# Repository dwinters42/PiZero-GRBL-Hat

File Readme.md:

# PiZero GRBL hat

This is a RaspberryPi Zero-compatible add-on board that can be used to
control up to 2 stepper motors using GCode commands. The board works
with the non-Wifi (Pi Zero) and the Wifi version (Pi Zero W), it
should also work with a standard Raspberrypi, although I have not
tested this.

The hat has an on-board AVR Mega328P micro-controller that runs the
[GRBL](https://github.com/grbl/grbl) firmware, 2 sockets for
Pololu-compatible Stepper boards and connectors for the stepper
motors, limit switches, stepper motor power and an extra I2C connector
that is wired to the Pi Zero I2C contacts.

The big benefit of this arrangement is that the AVR takes care of all
the timing-sensitive tasks, so that the Pi Zero can do other things.

# Building instructions
## Get components

See the bill of materials below.

## Assemble board

Use the [HTML-BOM](file:./bom_interactive.html) generated by the
brilliant [Interactive BOM KICAD plugin from
openscopeproject](https://github.com/openscopeproject/InteractiveHtmlBom)
to populate the board.

## Program firmware on AVR

## Mount the board

With the Raspberrypi turned off, plug the GRBL hat board into the Pi
header, so that the 2 boards are aligned to each other. Do not connect
anything to the GRBL hat yet.

## Pi Zero setup

In order for the communication to work, the on-board serial board of
the Raspberrypi has to be enabled with raspi-config: run raspi-config
in a terminal, go to Interfacing Options -> Serial -> No to login
shell -> Yes to enable serial port hardware. After rebooting, you
should have a new serial port accessible as /dev/ttyS0.

## Test serial connection

Connect to Grbl using the serial terminal of your choice. Set
the port to /dev/ttyS0 and the the baud rate to 115200, 8 bits, no
parity, 1 stop bit (8N1). One possibility is to use miniterm:

    miniterm /dev/ttyS0 115200

Once connected, you will not see anything (GRBL started when the Pi
was plugged into power).

Type $ and press enter to have GRBL print a help message. You should
not see any local echo of the $ and enter. Grbl should respond with:

    [HLP:$$ $# $G $I $N $x=val $Nx=line $J=line $SLP $C $X $H ~ ! ? ctrl-x]
    ok

Congratulations, you have a working GRBL controller connected to your
Pi Zero!

Shut down the Pi and disconnect power.

Next, connect two stepper driver boards (e.g. 2x Pololu DRV8825 driver
board). Make sure you get the orientation correct.

Then connect the motor power supply and set the current using the
trimpot on the driver boards. Disconnect motor power, plug in 2
stepper motors (e.g. NEMA17 form factor) and apply motor power again.

## First trial run

Turn on power to the Pi and log in via ssh. Run the following commands
from a terminal to test the motors:

    stty -F /dev/ttyS0 115200 # set baud rate to 115200 baud
	cat testing/test.gcode > /dev/ttyS0

This should move first the x-axis to 45 degrees and back, followed by
the y-axis. If there is jerky motion or no motion at all, make sure
that the wire connections to the steppers are good.

# Using the board

The Raspberrypi board communicates with the GRBL controller over the
on-board serial port /dev/ttyS0. The serial port needs to be
configured to 115200 baud, 8 databits, 1 stopbit, no parity (8N1).

The stepper resolution is set to 32 microsteps in hardware, this
cannot be changed. For a standard stepper with 200 steps per
revolution this gives 200*32/360 = 17.778 steps per degree.

Look at the well-maintained [GRBL
Wiki](https://github.com/gnea/grbl/wiki) for any GRBL related
questions.

# Bill of materials

|-------|-----|------------------|---------------------|--------------|-------------------|-------|
| Ref   | Qty | Value            | Part                | Manufacturer | Mouser            | Price |
|-------|-----|------------------|---------------------|--------------|-------------------|-------|
| A1    | 1   | AXIS_X           |                     | Pololu       |                   |       |
| A2    | 1   | AXIS_Y           |                     | Pololu       |                   |       |
| C1 C2 | 2   | 100n 0805        |                     |              |                   |       |
| C4 C5 | 2   | 33p 0805         |                     |              |                   |       |
| C8 C9 | 2   | 100u dia 6.3 25V |                     |              |                   |       |
| J1    | 1   | GPIO_CONNECTOR   | pin header 2x20     |              |                   |       |
| J2    | 1   | ISP              | pin header 2x03     |              |                   |       |
| J3    | 1   | LIMIT_X          | PH B2B 1x02 vert    | JST          |                   |       |
| J4    | 1   | LIMIT_Y          | PH B2B 1x02 vert    |              |                   |       |
| J5    | 1   | VMOT             | PH B2B 1x02 vert    |              |                   |       |
| J6    | 1   | MOTOR_X          | PH B2B 1x04 vert    |              |                   |       |
| J7    | 1   | MOTOR_Y          | PH B2B 1x04 vert    |              |                   |       |
| J8    | 1   | I2C              | PH B2B 1x04 vert    |              |                   |       |
| R1    | 1   | 1M 0805          |                     |              |                   |       |
| R2    | 1   | 10K 0805         |                     |              |                   |       |
| U1    | 1   | uC TQFP-32       | ATmega328P-AU       | Microchip    | 556-ATMEGA328P-AU | 1.81  |
| Y1    | 1   | 16MHz ABM3       | ABM3-16.000MHZ-B2-T | Abracon      | 815-ABM3-16-D2Y-T | 0.468 |
|-------|-----|------------------|---------------------|--------------|-------------------|-------|

# Todo for next revision

- add comment about 32 microsteps on schematics
- use less pins on the Raspi connector + cutout in PCB
- add missing mouser part numbers in BOM

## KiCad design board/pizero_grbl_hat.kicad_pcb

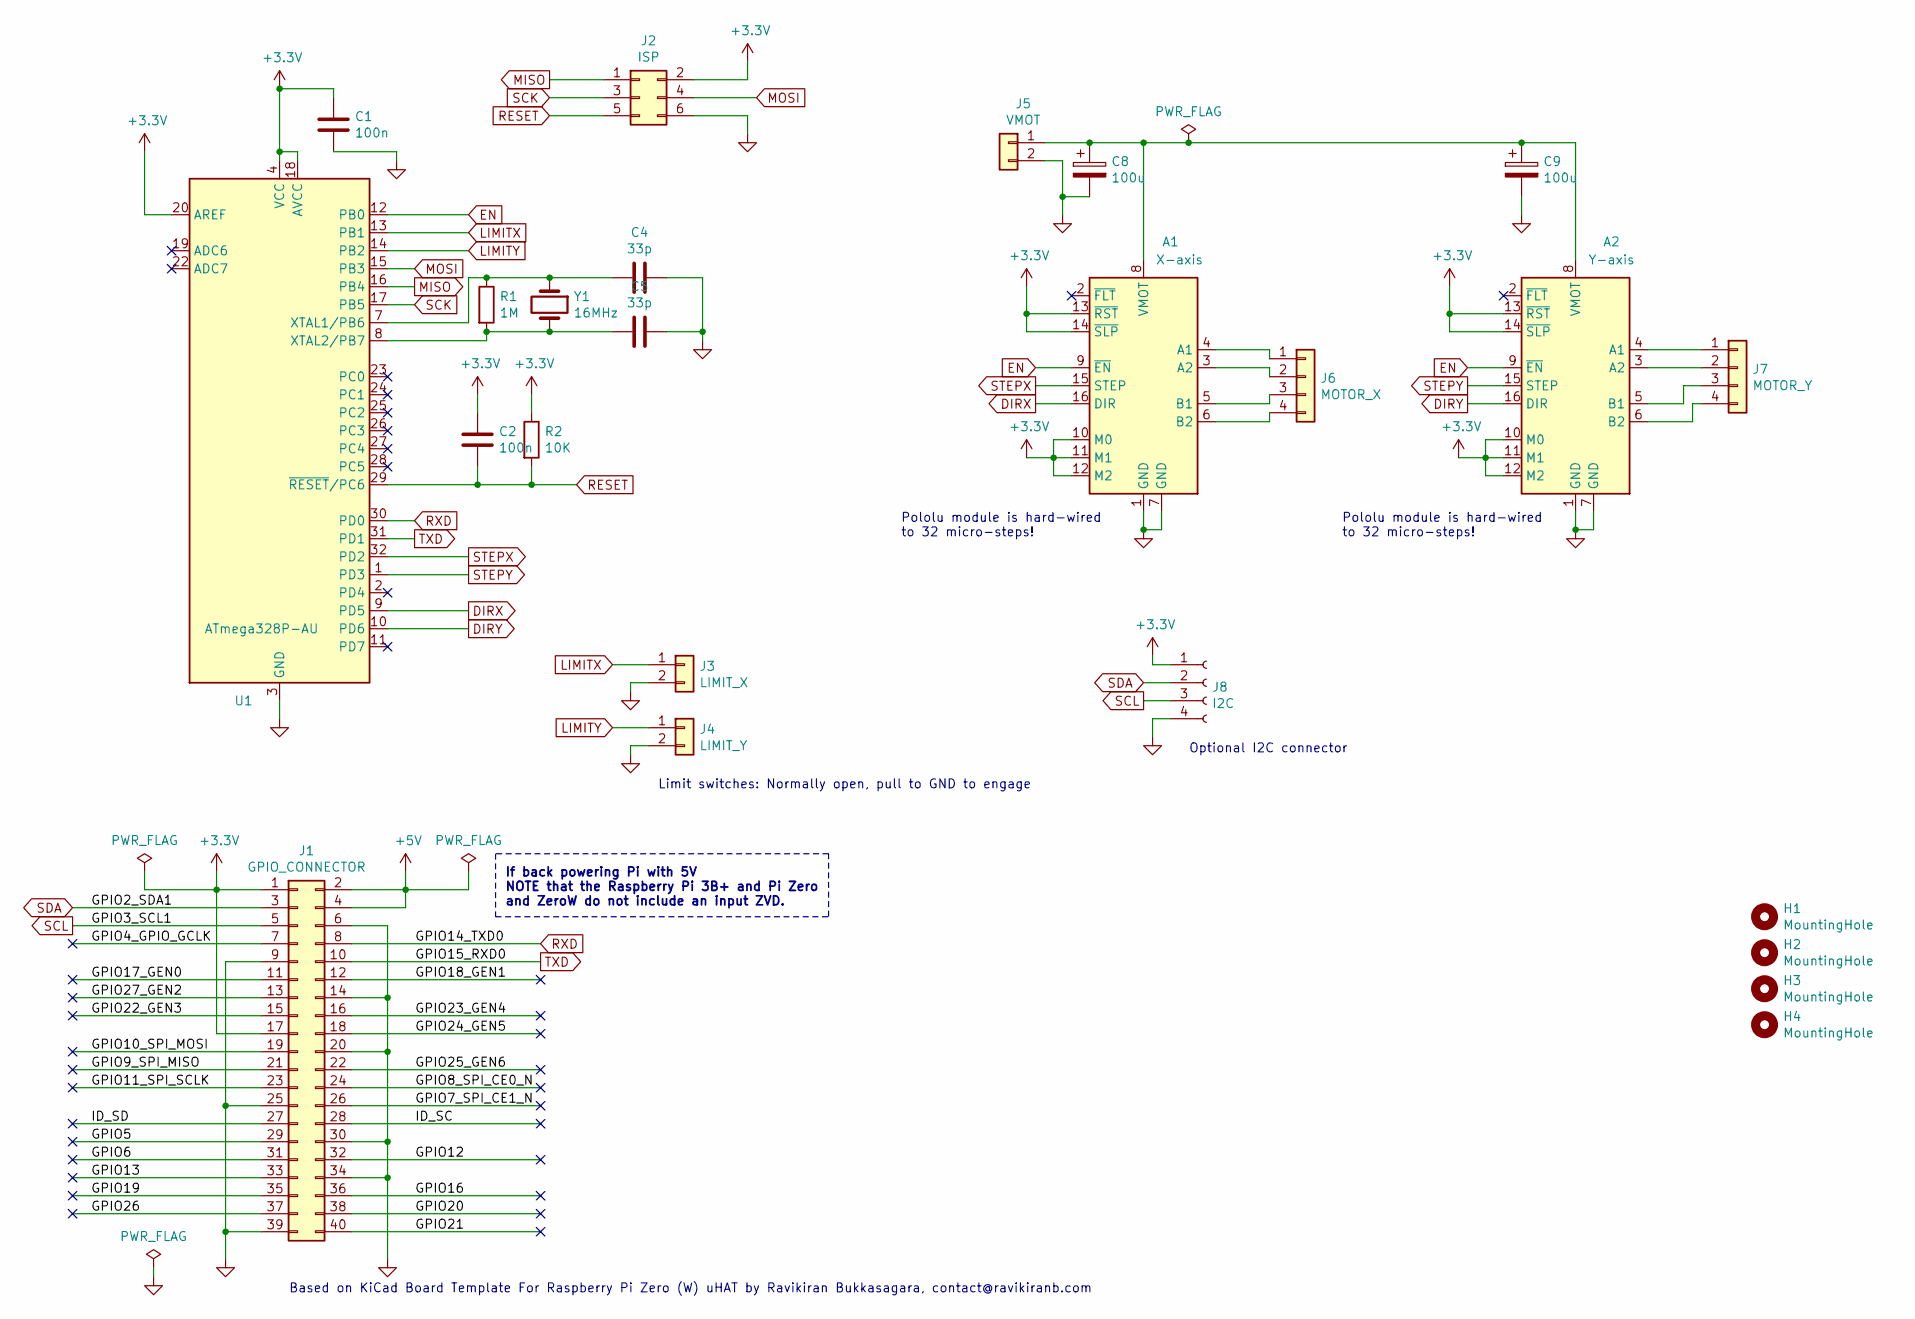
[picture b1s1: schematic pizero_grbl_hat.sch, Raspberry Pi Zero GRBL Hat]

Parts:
A1: X-axis; Pololu_Breakout-16_15.2x20.3mm
A2: Y-axis; Pololu_Breakout-16_15.2x20.3mm
C1: 100n; C_0805_2012Metric_Pad1.15x1.40mm_HandSolder
C2: 100n; C_0805_2012Metric
C4, C5: 33p; C_0805_2012Metric
C8, C9: 100u; CP_Elec_6.3x7.7
H1, H2, H3, H4: MountingHole; MountingHole_2.7mm_M2.5_uHAT_RPi
J1: GPIO_CONNECTOR; PinSocket_2x20_P2.54mm_Vertical_Centered_Anchor
J2: ISP; PinHeader_2x03_P2.54mm_Vertical
J3: LIMIT_X; JST_PH_B2B-PH-K_1x02_P2.00mm_Vertical
J4: LIMIT_Y; JST_PH_B2B-PH-K_1x02_P2.00mm_Vertical
J5: VMOT; JST_PH_B2B-PH-K_1x02_P2.00mm_Vertical
J6: MOTOR_X; JST_PH_B4B-PH-K_1x04_P2.00mm_Vertical
J7: MOTOR_Y; JST_PH_B4B-PH-K_1x04_P2.00mm_Vertical
J8: I2C; JST_PH_B4B-PH-K_1x04_P2.00mm_Vertical
R1: 1M; R_0805_2012Metric_Pad1.15x1.40mm_HandSolder
R2: 10K; R_0805_2012Metric
U1: ATmega328P-AU; TQFP-32_7x7mm_P0.8mm
Y1: 16MHz; Crystal_SMD_Abracon_ABM3-2Pin_5.0x3.2mm_HandSoldering

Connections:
+3V3: A1.10 (M0), A1.11 (M1), A1.12 (M2), A1.13 (~RST), A1.14 (~SLP), A2.10 (M0), A2.11 (M1), A2.12 (M2), A2.13 (~RST), A2.14 (~SLP), C1.1, C2.1, J1.1, J1.17, J2.2, J8.1, R2.1, U1.4 (VCC), U1.6 (VCC), U1.18 (AVCC), U1.20 (AREF)
+5V: J1.2, J1.4
/GPIO4_GPIO_GCLK: J1.7
/GPIO5: J1.29
/GPIO6: J1.31
/GPIO7_SPI_CE1_N: J1.26
/GPIO8_SPI_CE0_N: J1.24
/GPIO9_SPI_MISO: J1.21
/GPIO10_SPI_MOSI: J1.19
/GPIO11_SPI_SCLK: J1.23
/GPIO12: J1.32
/GPIO13: J1.33
/GPIO16: J1.36
/GPIO17_GEN0: J1.11
/GPIO18_GEN1: J1.12
/GPIO19: J1.35
/GPIO20: J1.38
/GPIO21: J1.40
/GPIO22_GEN3: J1.15
/GPIO23_GEN4: J1.16
/GPIO24_GEN5: J1.18
/GPIO25_GEN6: J1.22
/GPIO26: J1.37
/GPIO27_GEN2: J1.13
/ID_SC: J1.28
/ID_SD: J1.27
DIRX: A1.16 (DIR), U1.9 (PD5)
DIRY: A2.16 (DIR), U1.10 (PD6)
EN: A1.9 (~EN), A2.9 (~EN), U1.12 (PB0)
GND: A1.1 (GND), A1.7 (GND), A2.1 (GND), A2.7 (GND), C1.2, C4.1, C5.1, C8.2, C9.2, J1.6, J1.9, J1.14, J1.20, J1.25, J1.30, J1.34, J1.39, J2.6, J3.2, J4.2, J5.2, J8.4, U1.3 (GND), U1.5 (GND), U1.21 (GND)
LIMITX: J3.1, U1.13 (PB1)
LIMITY: J4.1, U1.14 (PB2)
MISO: J2.1, U1.16 (PB4)
MOSI: J2.4, U1.15 (PB3)
unnamed: A1.3 (A2), J6.2
unnamed: A1.4 (A1), J6.1
unnamed: A1.5 (B1), J6.3
unnamed: A1.6 (B2), J6.4
unnamed: A1.8 (VMOT), A2.8 (VMOT), C8.1, C9.1, J5.1
unnamed: A2.3 (A2), J7.2
unnamed: A2.4 (A1), J7.1
unnamed: A2.5 (B1), J7.3
unnamed: A2.6 (B2), J7.4
unnamed: C4.2, R1.1, U1.7 (XTAL1/PB6), Y1.1
unnamed: C5.2, R1.2, U1.8 (XTAL2/PB7), Y1.2
RESET: C2.2, J2.5, R2.2, U1.29 (~RESET~/PC6)
RXD: J1.8, U1.30 (PD0)
SCK: J2.3, U1.17 (PB5)
SCL: J1.5, J8.3
SDA: J1.3, J8.2
STEPX: A1.15 (STEP), U1.32 (PD2)
STEPY: A2.15 (STEP), U1.1 (PD3)
TXD: J1.10, U1.31 (PD1)

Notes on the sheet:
If back powering Pi with 5V NOTE that the Raspberry Pi 3B+ and Pi Zero and ZeroW do not include an input ZVD.
Based on KiCad Board Template For Raspberry Pi Zero (W) uHAT by Ravikiran Bukkasagara, contact@ravikiranb.com
Limit switches: Normally open, pull to GND to engage
Optional I2C connector
Pololu module is hard-wired to 32 micro-steps!

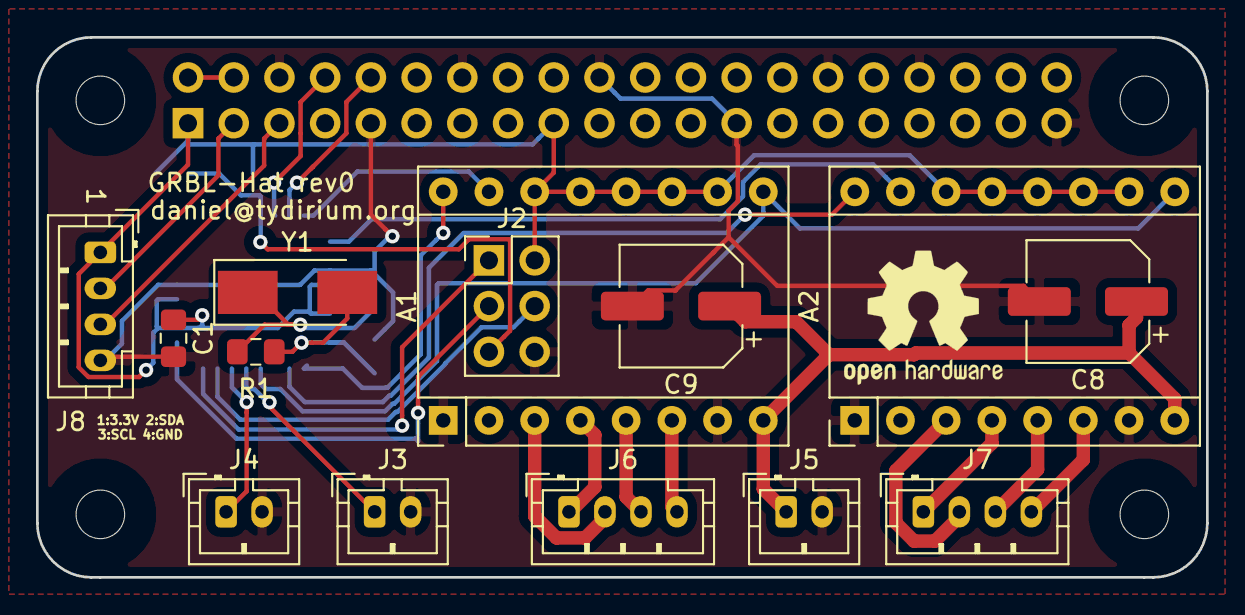
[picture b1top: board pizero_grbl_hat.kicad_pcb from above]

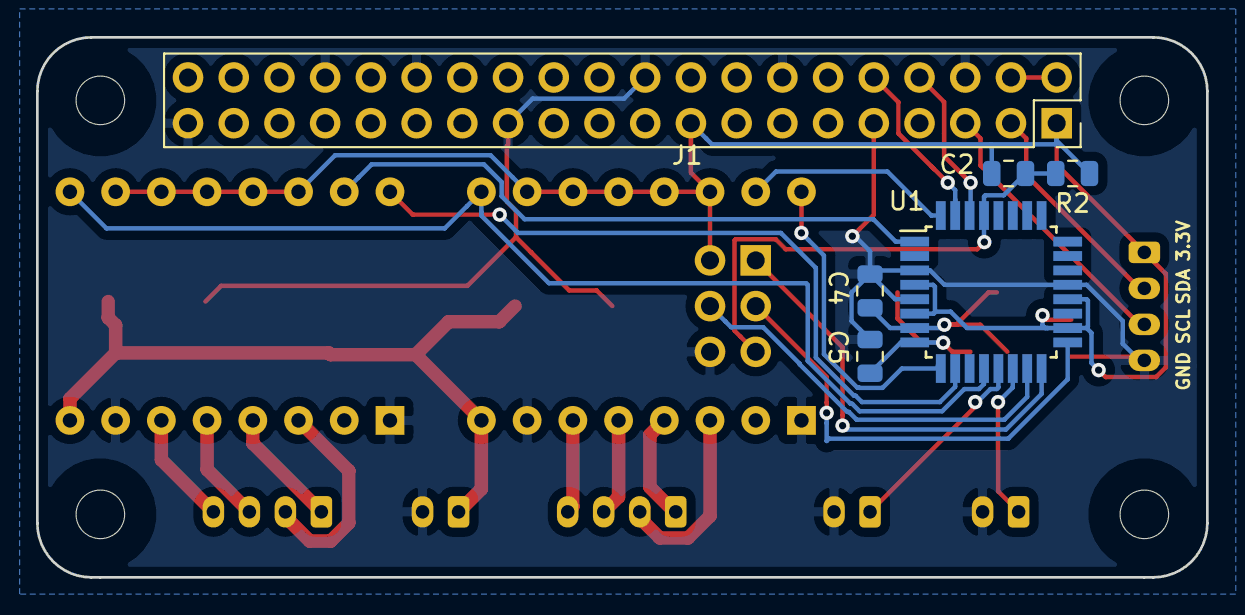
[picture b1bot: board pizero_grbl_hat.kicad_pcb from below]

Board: 2 copper layers, 65.0 x 30.0 mm, 24 parts (6 on the bottom side), 29 nets.

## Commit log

2019-11-20 add .gitignore
2019-11-20 initial import, work in progress
2019-11-20 finish schematics, start assigning packages
2019-11-21 layout mostly done
2019-11-27 finish layout and print schematics
2019-11-29 create BOM and start Readme
2020-02-09 start working on rev1, work in progress
2020-02-09 move Kicad board files to a subdirectory
2020-02-09 mv bill of materials around
2020-02-09 move the schematics into a documentation folder
2020-03-04 flesh out the Readme with build and test instructions
2020-03-04 add a few todo items for the next revision
2020-03-20 show I2C pins on front and back silkscreen
2020-04-22 add open hardware logo on the board
2020-04-22 better .gitignore
2020-04-26 replace Readme.md with org-mode version; small improvements
2020-04-26 ignore .DS_Store everywhere
2020-04-26 dome doc updates to schematics
2020-04-26 use AVR symbol from the standard library instead of rescue lib
2020-04-26 remove 2 unneeded files
2020-04-26 move interactive bom to documentation/
2020-04-26 add a rendering of the board (without the Pololu modules)
2020-04-26 add LICENSE
2020-04-26 fix link to BOM

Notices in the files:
board/pizero_grbl_hat.kicad_pcb:
This PCB design is licensed under MIT Open Source License.
board/pizero_grbl_hat.sch:
MIT License
